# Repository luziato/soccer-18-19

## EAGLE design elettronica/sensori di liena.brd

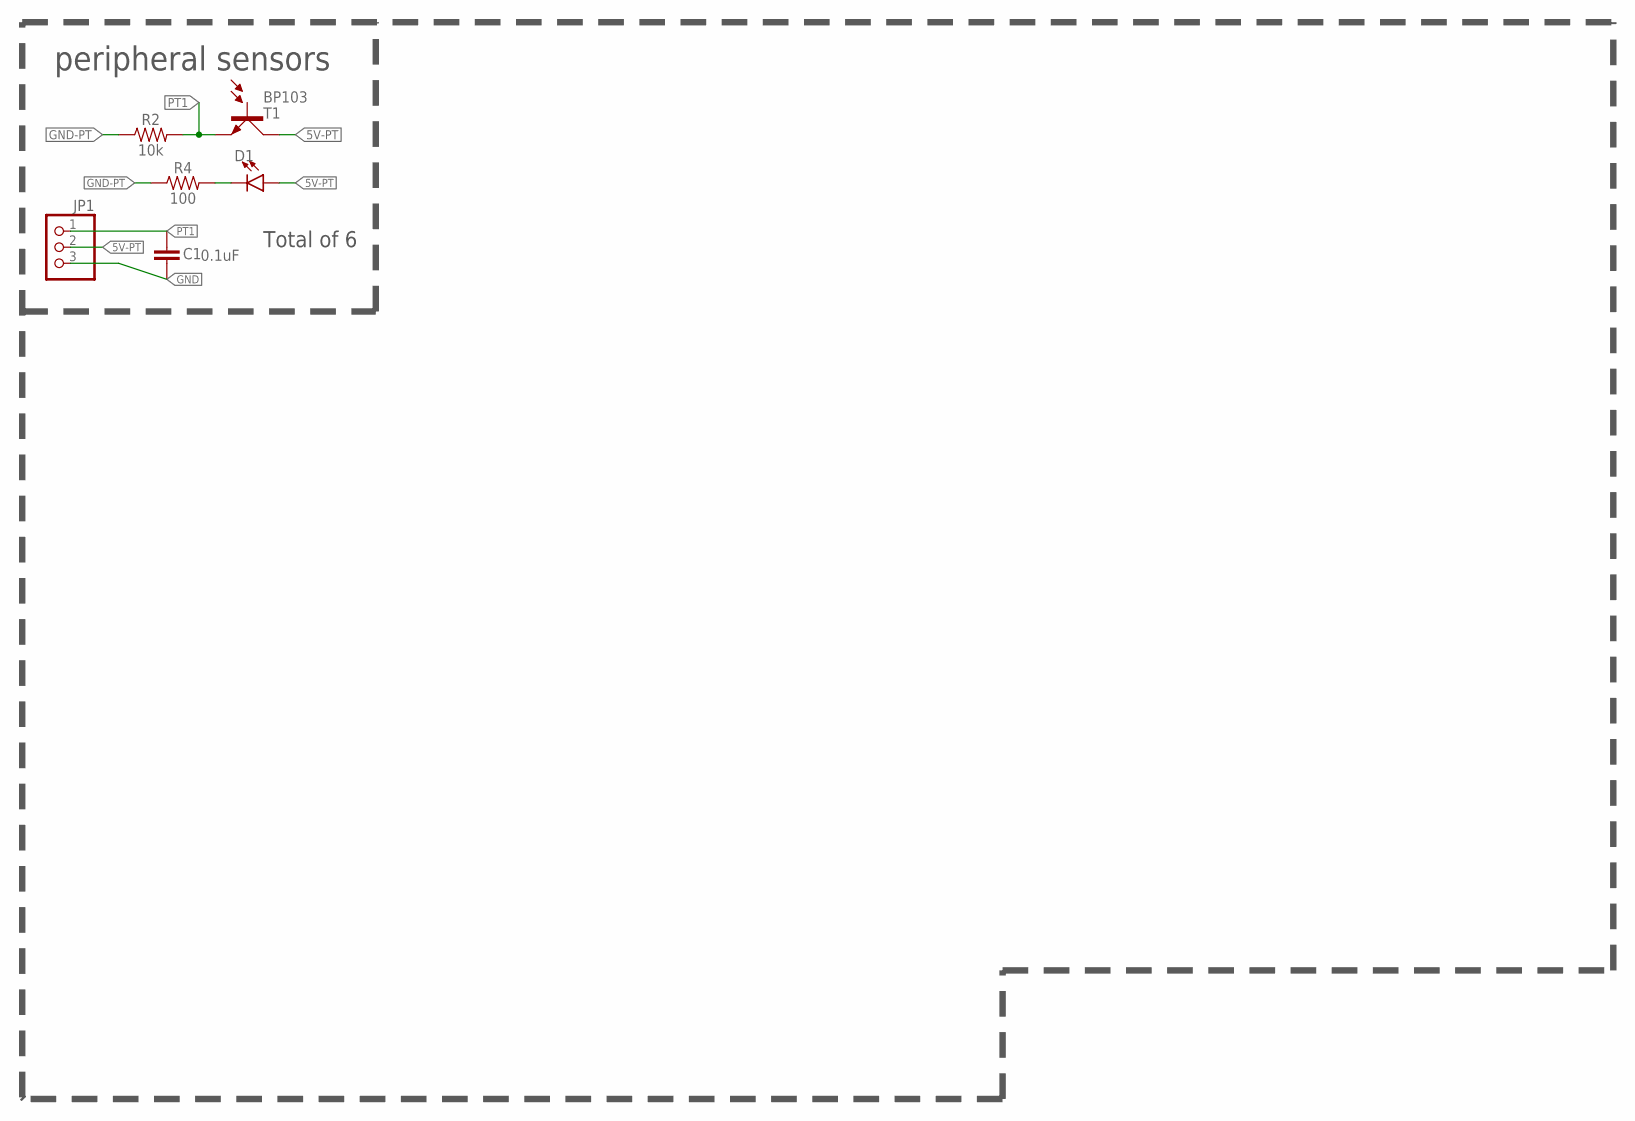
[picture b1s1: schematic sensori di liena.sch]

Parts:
C1: 0.1uF; CAP-PTH-SMALL-KIT
D1: LED3MM; LED_3MM
JP1: PINHD-1X3; 1X03
R2: 10k; 0603
R4: 100; 0603
T1: BP103

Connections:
5V-PT: D1.A, JP1.2, T1.C
GND: C1.2, JP1.3
GND-PT: R2.1, R4.1
unnamed: D1.K (C), R4.2
PT1: C1.1, JP1.1, R2.2, T1.E

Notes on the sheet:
peripheral sensors
Total of 6

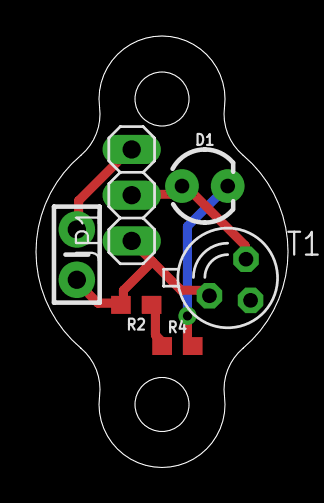
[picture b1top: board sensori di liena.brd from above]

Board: 2 copper layers, 14.0 x 24.0 mm, 6 parts (0 on the bottom side), 5 nets.

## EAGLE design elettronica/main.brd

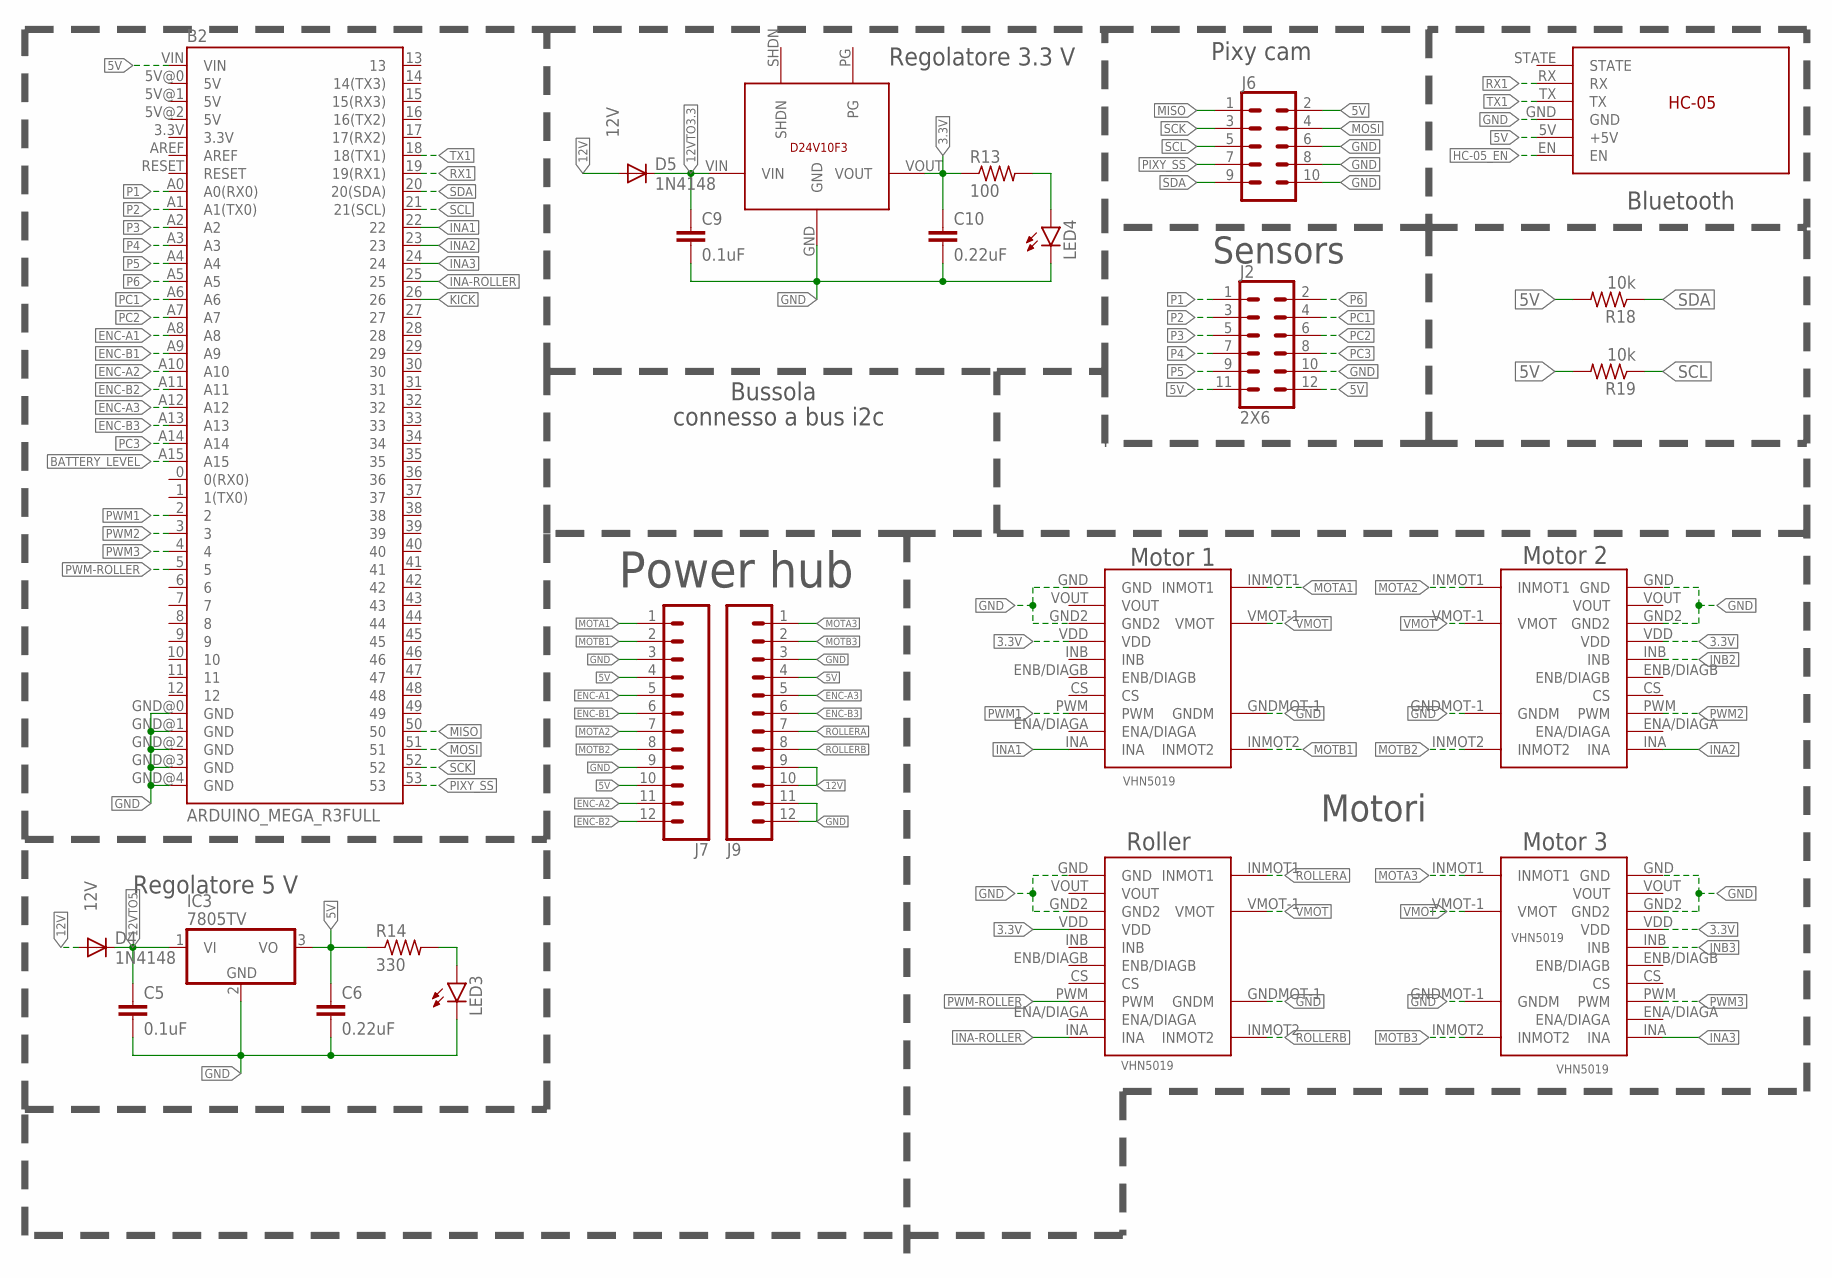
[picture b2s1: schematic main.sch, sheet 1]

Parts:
B2: ARDUINO_MEGA_R3FULL; ARDUINO_MEGA
C5, C9: 0.1uF; CAP-PTH-SMALL-KIT
C6, C10: 0.22uF; CAP-PTH-SMALL-KIT
D4, D5: 1N4148; DO35-7
IC3: 7805TV; TO220V
J2: 2X6
J6: CONN_05X2PTH; 2X5
J7, J9: CONN_12; 1X12
LED3, LED4: GREEN; LED-1206
R13: 100; M1206
R14: 330; M1206
R18, R19: 10k; M1206
U$4, U$5, U$6, U$7: VHN5019; MOTOR-SHIELD
U$18: HC-05
U$19: STEPDOWN_D24V10F3

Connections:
3.3V: C10.1, R13.1, U$4.VDD, U$5.VDD, U$6.VDD, U$7.VDD, U$19.VOUT; also elsewhere on the board
5V: B2.VIN, C6.1, IC3.3 (VO), J2.11, J2.12, J6.2, J7.4, J7.10, J9.4, R14.1, R18.2, R19.2, U$18.5V (+5V); also elsewhere on the board
12V: D4.A, D5.A, J9.9, J9.10; also elsewhere on the board
12VTO3.3: C9.1, D5.C, U$19.VIN
12VTO5: C5.1, D4.C, IC3.1 (VI)
BATTERY_LEVEL: B2.A15; also elsewhere on the board
ENC-A1: B2.A8, J7.5
ENC-A2: B2.A10, J7.11
ENC-A3: B2.A12, J9.5
ENC-B1: B2.A9, J7.6
ENC-B2: B2.A11, J7.12
ENC-B3: B2.A13, J9.6
GND: B2.GND@0 (GND), B2.GND@1 (GND), B2.GND@2 (GND), B2.GND@3 (GND), B2.GND@4 (GND), C5.2, C6.2, C9.2, C10.2, IC3.2 (GND), J2.10, J6.6, J6.8, J6.10, J7.3, J7.9, J9.3, J9.11, J9.12, LED3.C, LED4.C, U$4.GND, U$4.GND2, U$4.GNDMOT-1 (GNDM), U$5.GND, U$5.GND2, U$5.GNDMOT-1 (GNDM), U$6.GND, U$6.GND2, U$6.GNDMOT-1 (GNDM), U$7.GND, U$7.GND2, U$7.GNDMOT-1 (GNDM), U$18.GND, U$19.GND; also elsewhere on the board
HC-05_EN: U$18.EN
INA1: B2.22, U$4.INA
INA2: B2.23, U$5.INA
INA3: B2.24, U$6.INA
INA-ROLLER: B2.25, U$7.INA
INB2: U$5.INB
INB3: U$6.INB
KICK: B2.26; also elsewhere on the board
MISO: B2.50, J6.1
MOSI: B2.51, J6.4
MOTA1: J7.1, U$4.INMOT1
MOTA2: J7.7, U$5.INMOT1
MOTA3: J9.1, U$6.INMOT1
MOTB1: J7.2, U$4.INMOT2
MOTB2: J7.8, U$5.INMOT2
MOTB3: J9.2, U$6.INMOT2
unnamed: LED3.A, R14.2
unnamed: LED4.A, R13.2
P1: B2.A0 (A0(RX0)), J2.1
P2: B2.A1 (A1(TX0)), J2.3
P3: B2.A2, J2.5
P4: B2.A3, J2.7
P5: B2.A4, J2.9
P6: B2.A5, J2.2
PC1: B2.A6, J2.4
PC2: B2.A7, J2.6
PC3: B2.A14, J2.8
PIXY_SS: B2.53, J6.7
PWM1: B2.2, U$4.PWM
PWM2: B2.3, U$5.PWM
PWM3: B2.4, U$6.PWM
PWM-ROLLER: B2.5, U$7.PWM
ROLLERA: J9.7, U$7.INMOT1
ROLLERB: J9.8, U$7.INMOT2
RX1: B2.19 (19(RX1)), U$18.RX
SCK: B2.52, J6.3
SCL: B2.21 (21(SCL)), J6.5, R19.1; also elsewhere on the board
SDA: B2.20 (20(SDA)), J6.9, R18.1; also elsewhere on the board
TX1: B2.18 (18(TX1)), U$18.TX
VMOT: U$4.VMOT-1 (VMOT), U$5.VMOT-1 (VMOT), U$6.VMOT-1 (VMOT), U$7.VMOT-1 (VMOT); also elsewhere on the board

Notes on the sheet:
Regolatore 5 V
Regolatore 3.3 V
Bluetooth
Bussola
Motori
Roller
Motor 1
Motor 2
Motor 3
Pixy cam
Sensors
Power hub
connesso a bus i2c

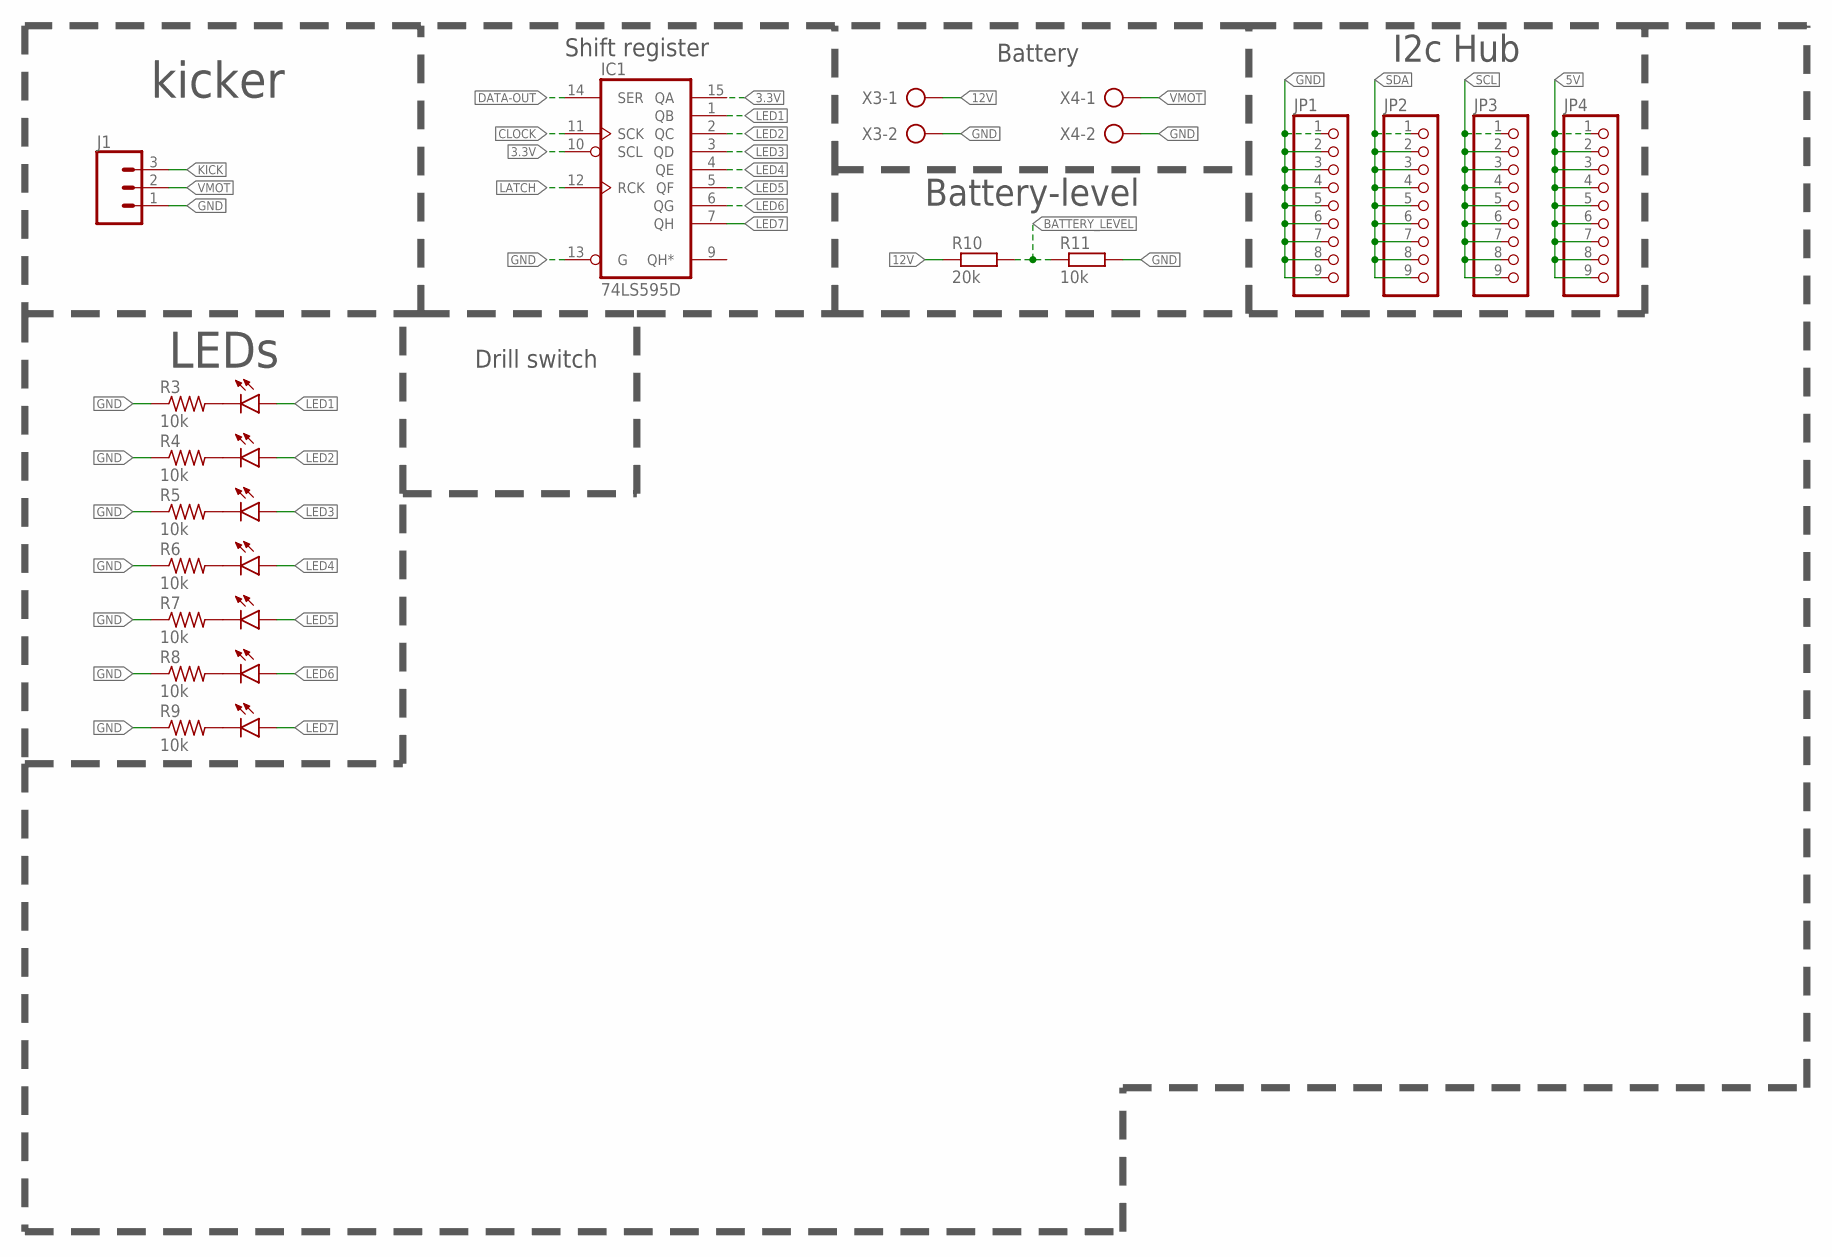
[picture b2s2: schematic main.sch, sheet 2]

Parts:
D1, D3, D6, D7, D8, D9, D10: GREEN; LED-1206
IC1: 74LS595D; SO16
J1: CONN_03; 1X03
JP1, JP2, JP3, JP4: PINHD-1X9; 1X09-BIG
R3, R4, R5, R6, R7, R8, R9: 10k; M1206
R10: 20k; 0204/7
R11: 10k; 0204/7
X3, X4: AK500/2-H

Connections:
3.3V: IC1.10 (SCL), IC1.15 (QA); also elsewhere on the board
5V: JP4.1, JP4.2, JP4.3, JP4.4, JP4.5, JP4.6, JP4.7, JP4.8, JP4.9; also elsewhere on the board
12V: R10.1, X3.1; also elsewhere on the board
BATTERY_LEVEL: R10.2, R11.1; also elsewhere on the board
CLOCK: IC1.11 (SCK)
DATA-OUT: IC1.14 (SER)
GND: IC1.8 (GND), IC1.13 (G), J1.1, JP1.1, JP1.2, JP1.3, JP1.4, JP1.5, JP1.6, JP1.7, JP1.8, JP1.9, R3.1, R4.1, R5.1, R6.1, R7.1, R8.1, R9.1, R11.2, X3.2, X4.2; also elsewhere on the board
KICK: J1.3; also elsewhere on the board
LATCH: IC1.12 (RCK)
LED1: D1.A, IC1.1 (QB)
LED2: D3.A, IC1.2 (QC)
LED3: D6.A, IC1.3 (QD)
LED4: D7.A, IC1.4 (QE)
LED5: D8.A, IC1.5 (QF)
LED6: D9.A, IC1.6 (QG)
LED7: D10.A, IC1.7 (QH)
unnamed: D1.C, R3.2
unnamed: D3.C, R4.2
unnamed: D6.C, R5.2
unnamed: D7.C, R6.2
unnamed: D8.C, R7.2
unnamed: D9.C, R8.2
unnamed: D10.C, R9.2
SCL: JP3.1, JP3.2, JP3.3, JP3.4, JP3.5, JP3.6, JP3.7, JP3.8, JP3.9; also elsewhere on the board
SDA: JP2.1, JP2.2, JP2.3, JP2.4, JP2.5, JP2.6, JP2.7, JP2.8, JP2.9; also elsewhere on the board
VCC: IC1.16 (VCC)
VMOT: J1.2, X4.1; also elsewhere on the board

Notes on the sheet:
Shift register
Battery
LEDs
Battery-level
Drill switch
I2c Hub
kicker

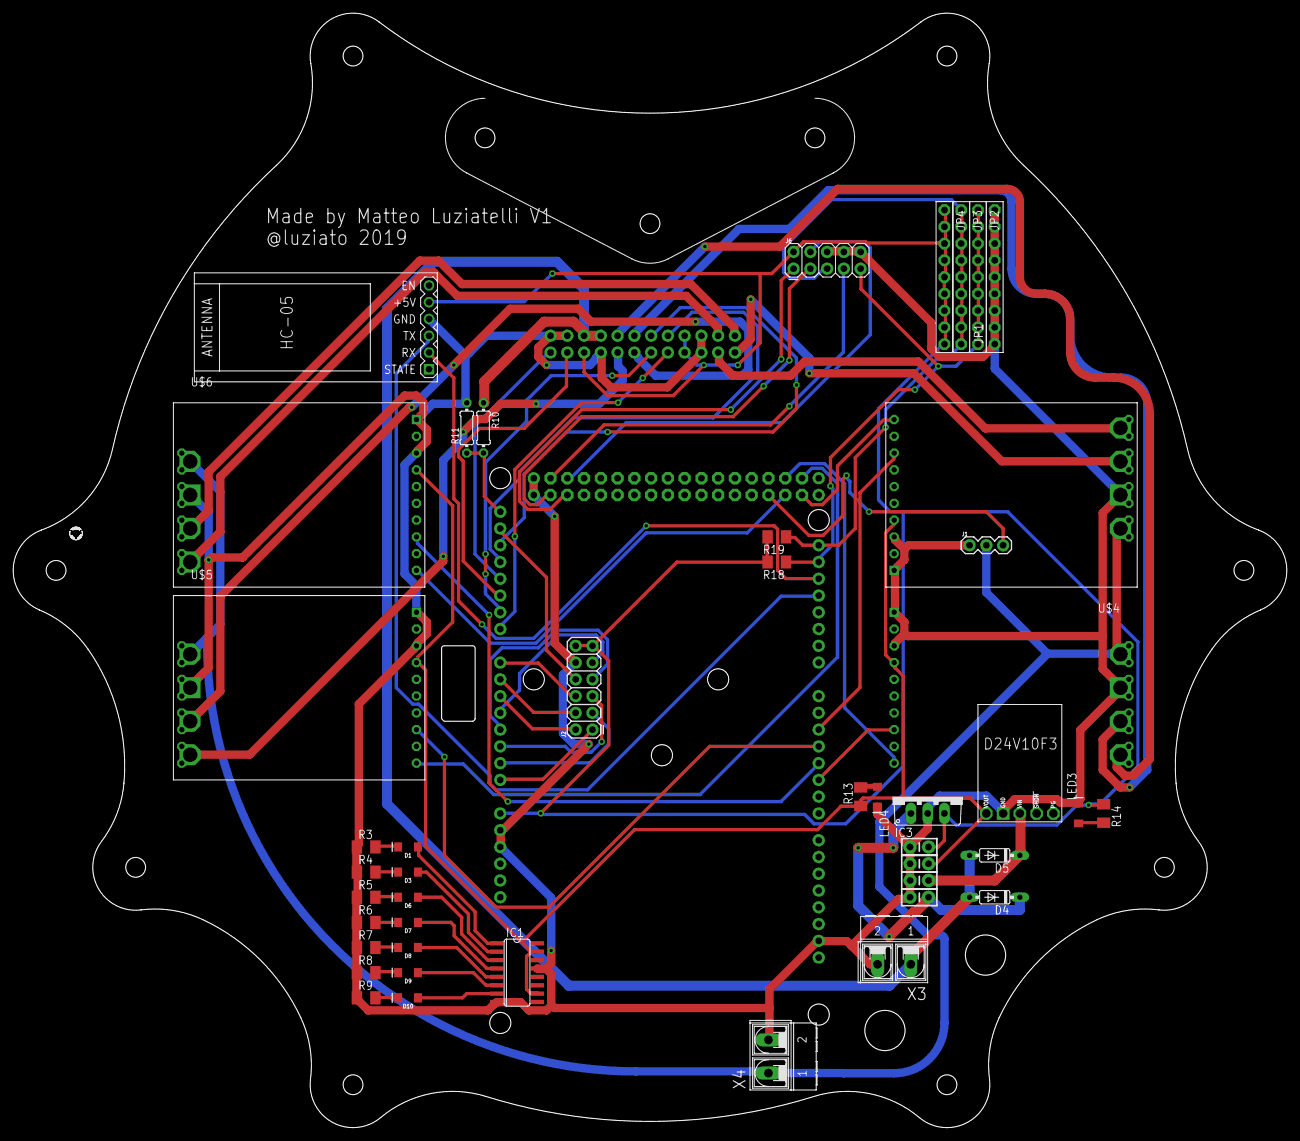
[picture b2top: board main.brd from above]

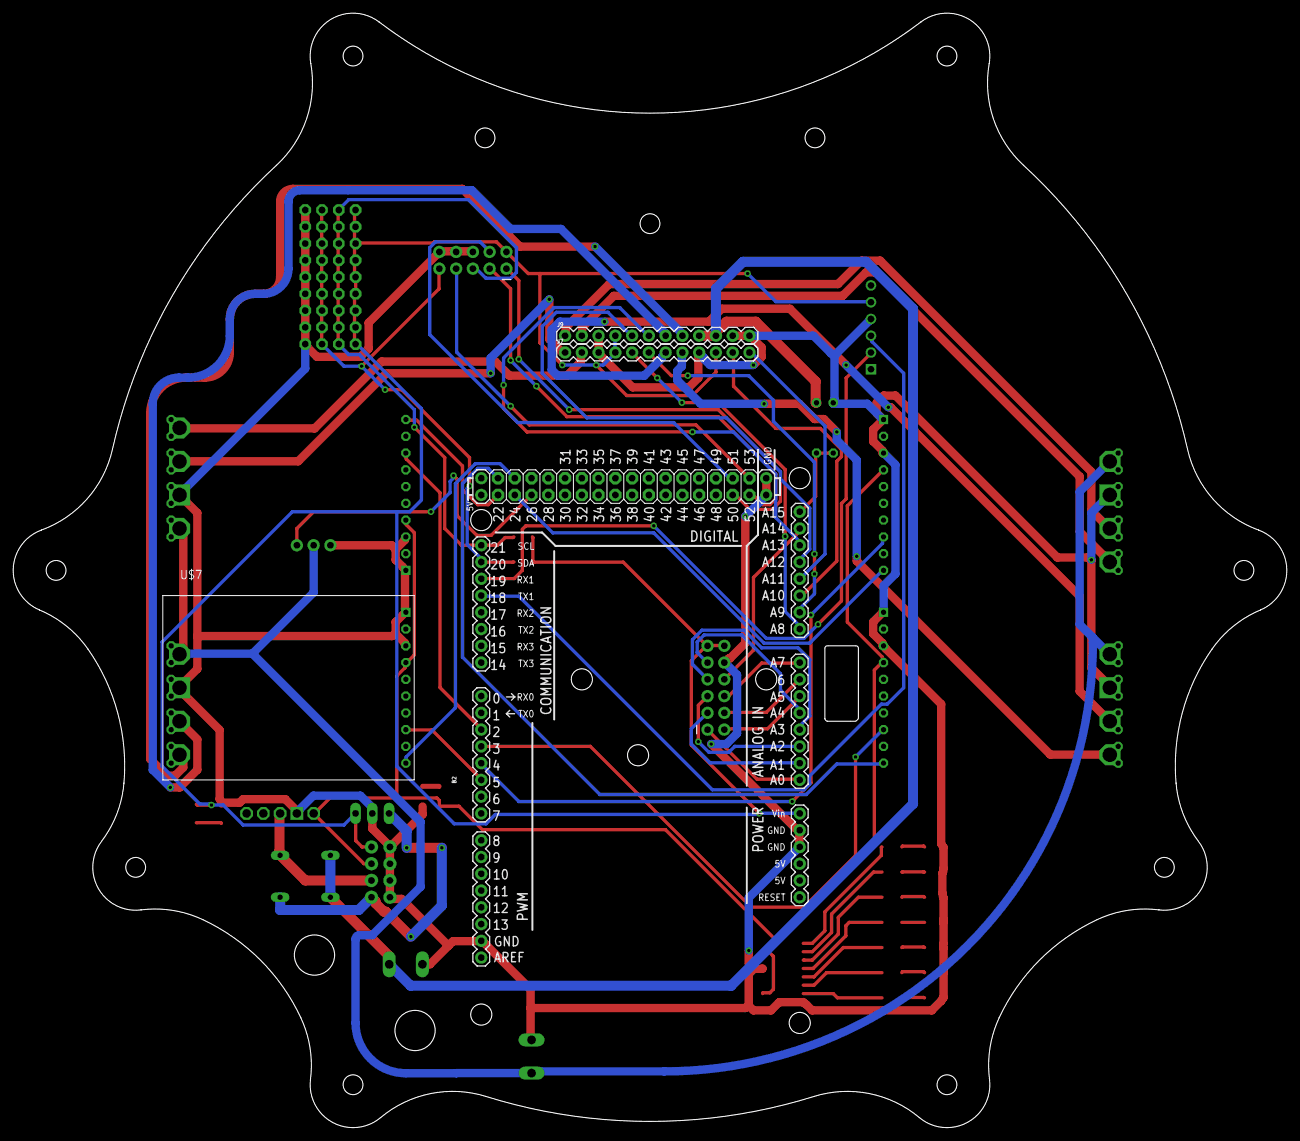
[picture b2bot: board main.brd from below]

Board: 2 copper layers, 193.0 x 168.9 mm, 48 parts (4 on the bottom side), 64 nets.

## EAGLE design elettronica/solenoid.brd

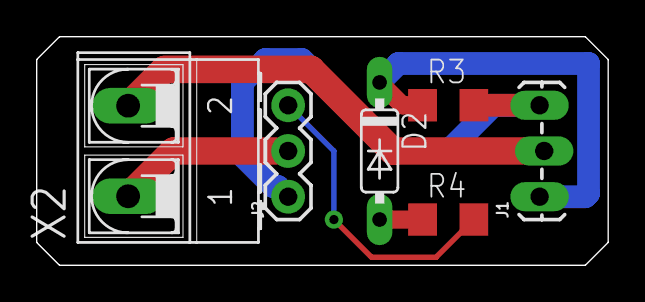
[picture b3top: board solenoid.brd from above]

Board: 2 copper layers, 31.8 x 12.7 mm, 6 parts (0 on the bottom side), 6 nets.

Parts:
D2: 1N4148; DO35-7
J1: stp16nf06; 1X03_LOCK_LONGPADS
J2: 1X03
R3: 10k; R1206
R4: 100; R1206
X2: AK500/2-H

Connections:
12V: J2.2, X2.1
DRAIN: J1.2, X2.2
GND: J1.3, J2.1, R3.2
KICK: J2.3, R4.2
unnamed: D2.C, J1.1, R3.1
unnamed: D2.A, R4.1

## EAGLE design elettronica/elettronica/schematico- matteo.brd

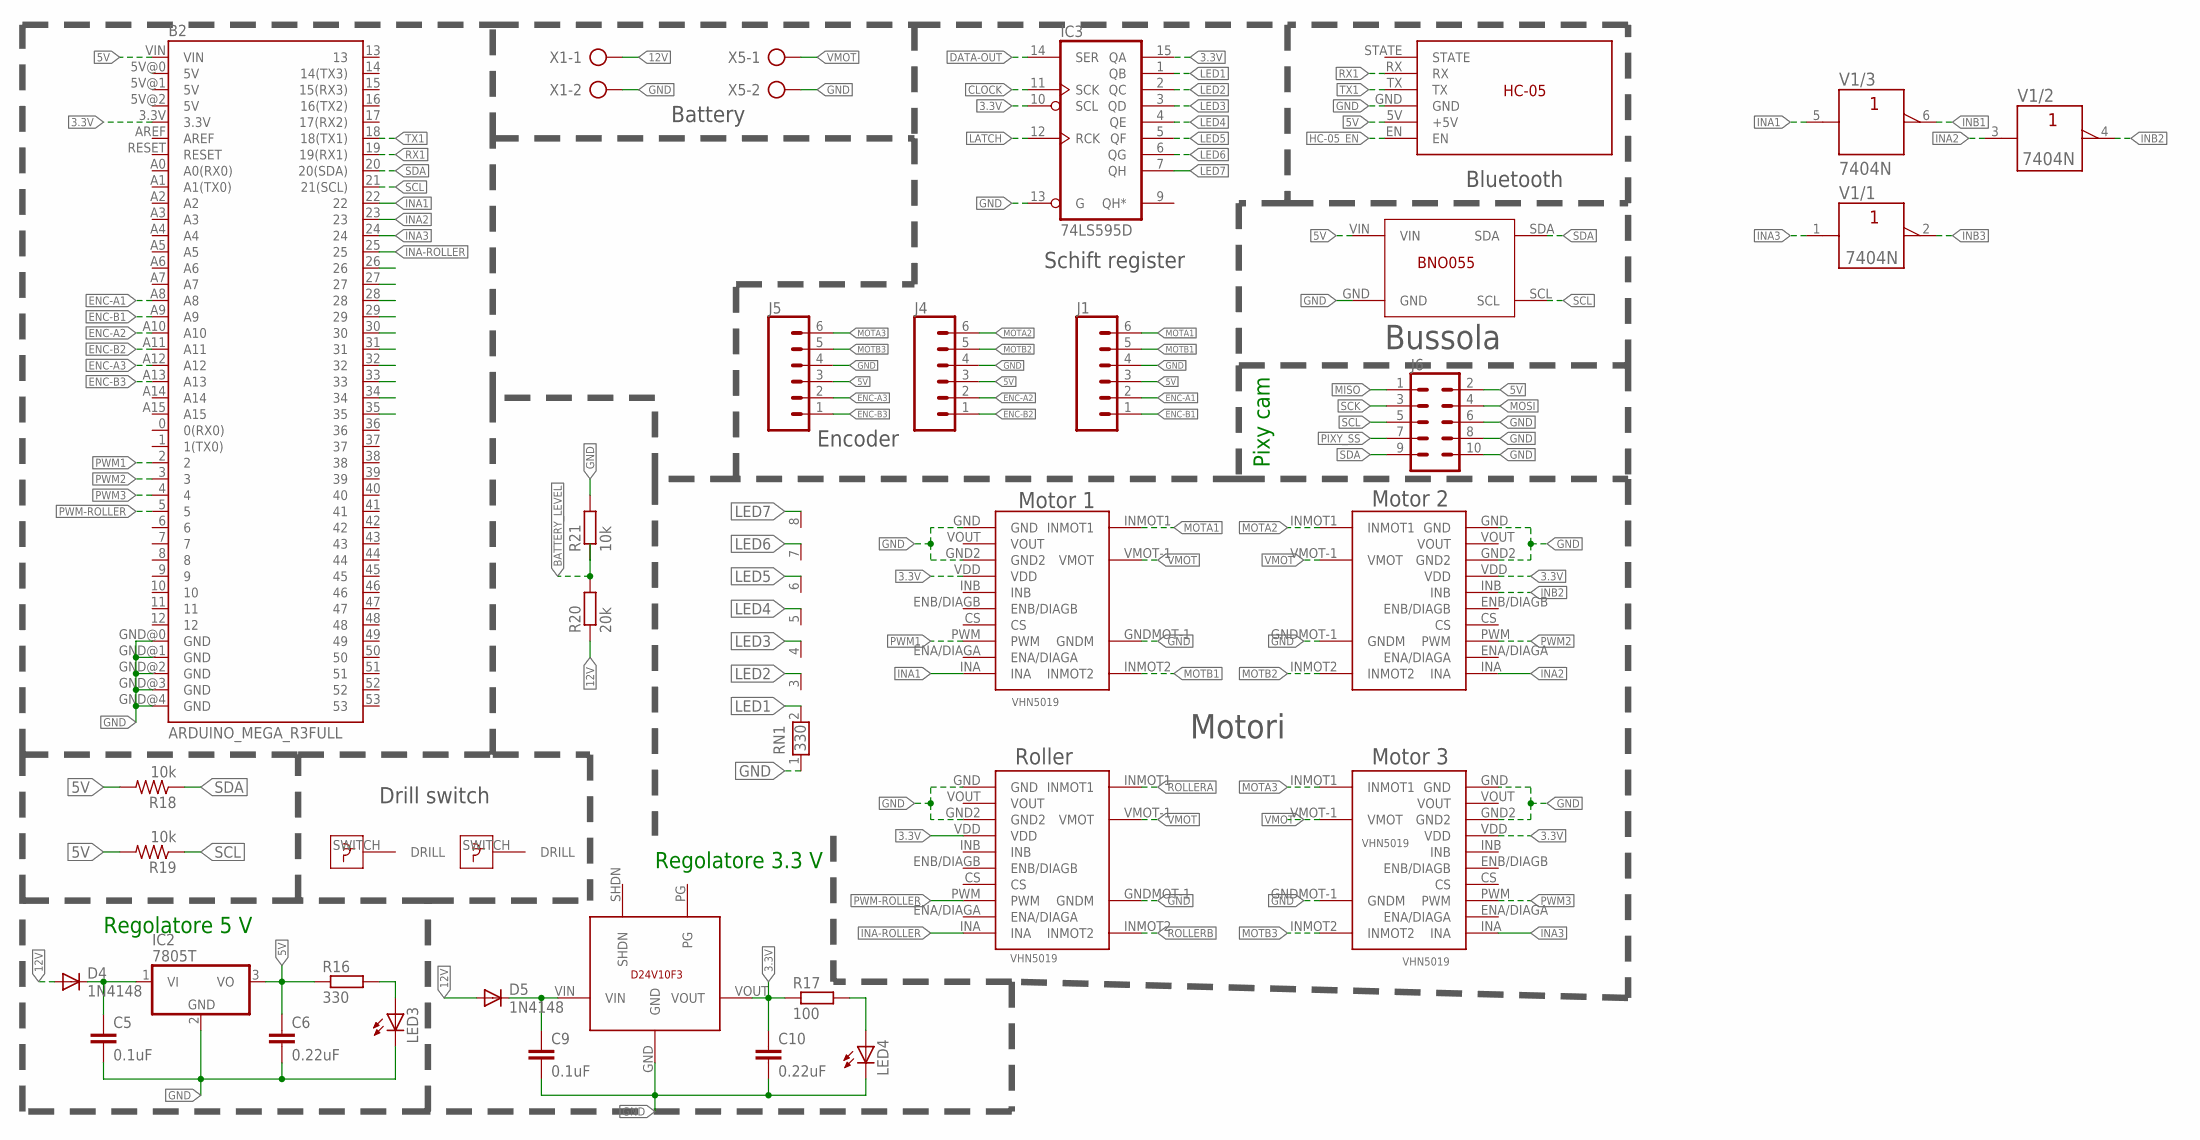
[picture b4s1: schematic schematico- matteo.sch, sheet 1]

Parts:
B2: ARDUINO_MEGA_R3FULL; ARDUINO_MEGA
C5, C9: 0.1uF; CAP-PTH-SMALL-KIT
C6, C10: 0.22uF; CAP-PTH-SMALL-KIT
D4, D5: 1N4148; DO35-7
IC2: 7805T; TO220H
IC3: 74LS595D; SO16
J1, J4, J5: CONN_06SILK_FEMALE_PTH; 1X06
J6: CONN_05X2PTH; 2X5
LED3, LED4: TLLR4400; LED3MM
R16: 330; 0204/7
R17: 100; 0204/7
R18, R19: 10k; M1206
R20: 20k; 0204/7
R21: 10k; 0204/7
RN1: 330; RN-8
U$1, U$2: DRILL_SWITCH
U$4, U$5, U$6, U$7: VHN5019; MOTOR-SHIELD
U$17: BNO055; BNO005
U$18: HC-05
U$19: STEPDOWN_D24V10F3
V1: 7404N; DIL14
X1, X5: AK500/2-H

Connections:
3.3V: B2.3.3V, C10.1, IC3.10 (SCL), IC3.15 (QA), R17.1, U$4.VDD, U$5.VDD, U$6.VDD, U$7.VDD, U$19.VOUT; also elsewhere on the board
5V: B2.VIN, C6.1, IC2.3 (VO), J1.3, J4.3, J5.3, J6.2, R16.1, R18.2, R19.2, U$17.VIN, U$18.5V (+5V); also elsewhere on the board
12V: C5.1, D4.A, D4.C, D5.A, IC2.1 (VI), R20.1, X1.1; also elsewhere on the board
+UB: V1.14 (+UB)
-UB: V1.7 (-UB)
BATTERY_LEVEL: R20.2, R21.1; also elsewhere on the board
CLOCK: IC3.11 (SCK)
DATA-OUT: IC3.14 (SER)
ENC-A1: B2.A8, J1.2
ENC-A2: B2.A10, J4.2
ENC-A3: B2.A12, J5.2
ENC-B1: B2.A9, J1.1
ENC-B2: B2.A11, J4.1
ENC-B3: B2.A13, J5.1
GND: B2.GND@0 (GND), B2.GND@1 (GND), B2.GND@2 (GND), B2.GND@3 (GND), B2.GND@4 (GND), C5.2, C6.2, C9.2, C10.2, IC2.2 (GND), IC3.8 (GND), IC3.13 (G), J1.4, J4.4, J5.4, J6.6, J6.8, J6.10, LED3.K (C), LED4.K (C), R21.2, RN1.1, U$4.GND, U$4.GND2, U$4.GNDMOT-1 (GNDM), U$5.GND, U$5.GND2, U$5.GNDMOT-1 (GNDM), U$6.GND, U$6.GND2, U$6.GNDMOT-1 (GNDM), U$7.GND, U$7.GND2, U$7.GNDMOT-1 (GNDM), U$17.GND, U$18.GND, U$19.GND, X1.2, X5.2; also elsewhere on the board
HC-05_EN: U$18.EN
INA1: B2.22, U$4.INA, V1.5 (A)
INA2: B2.23, U$5.INA, V1.3 (A)
INA3: B2.24, U$6.INA, V1.1 (A)
INA-ROLLER: B2.25, U$7.INA
INB1: V1.6 (Y)
INB2: U$5.INB, V1.4 (Y)
INB3: V1.2 (Y)
LATCH: IC3.12 (RCK)
LED1: IC3.1 (QB), RN1.2; also elsewhere on the board
LED2: IC3.2 (QC), RN1.3; also elsewhere on the board
LED3: IC3.3 (QD), RN1.4; also elsewhere on the board
LED4: IC3.4 (QE), RN1.5; also elsewhere on the board
LED5: IC3.5 (QF), RN1.6; also elsewhere on the board
LED6: IC3.6 (QG), RN1.7; also elsewhere on the board
LED7: IC3.7 (QH), RN1.8; also elsewhere on the board
MISO: J6.1; also elsewhere on the board
MOSI: J6.4; also elsewhere on the board
MOTA1: J1.6, U$4.INMOT1
MOTA2: J4.6, U$5.INMOT1
MOTA3: J5.6, U$6.INMOT1
MOTB1: J1.5, U$4.INMOT2
MOTB2: J4.5, U$5.INMOT2
MOTB3: J5.5, U$6.INMOT2
unnamed: LED3.A, R16.2
unnamed: C9.1, D5.C, U$19.VIN
unnamed: LED4.A, R17.2
PIXY_SS: J6.7; also elsewhere on the board
PWM1: B2.2, U$4.PWM
PWM2: B2.3, U$5.PWM
PWM3: B2.4, U$6.PWM
PWM-ROLLER: B2.5, U$7.PWM
ROLLERA: U$7.INMOT1
ROLLERB: U$7.INMOT2
RX1: B2.19 (19(RX1)), U$18.RX
SCK: J6.3; also elsewhere on the board
SCL: B2.21 (21(SCL)), J6.5, R19.1, U$17.SCL; also elsewhere on the board
SDA: B2.20 (20(SDA)), J6.9, R18.1, U$17.SDA; also elsewhere on the board
TX1: B2.18 (18(TX1)), U$18.TX
VCC: IC3.16 (VCC)
VMOT: U$4.VMOT-1 (VMOT), U$5.VMOT-1 (VMOT), U$6.VMOT-1 (VMOT), U$7.VMOT-1 (VMOT), X5.1; also elsewhere on the board

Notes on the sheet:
Regolatore 5 V
Regolatore 3.3 V
Encoder
Schift register
Bluetooth
Bussola
Motori
Roller
Battery
Drill switch
Motor 1
Motor 2
Motor 3
Pixy cam

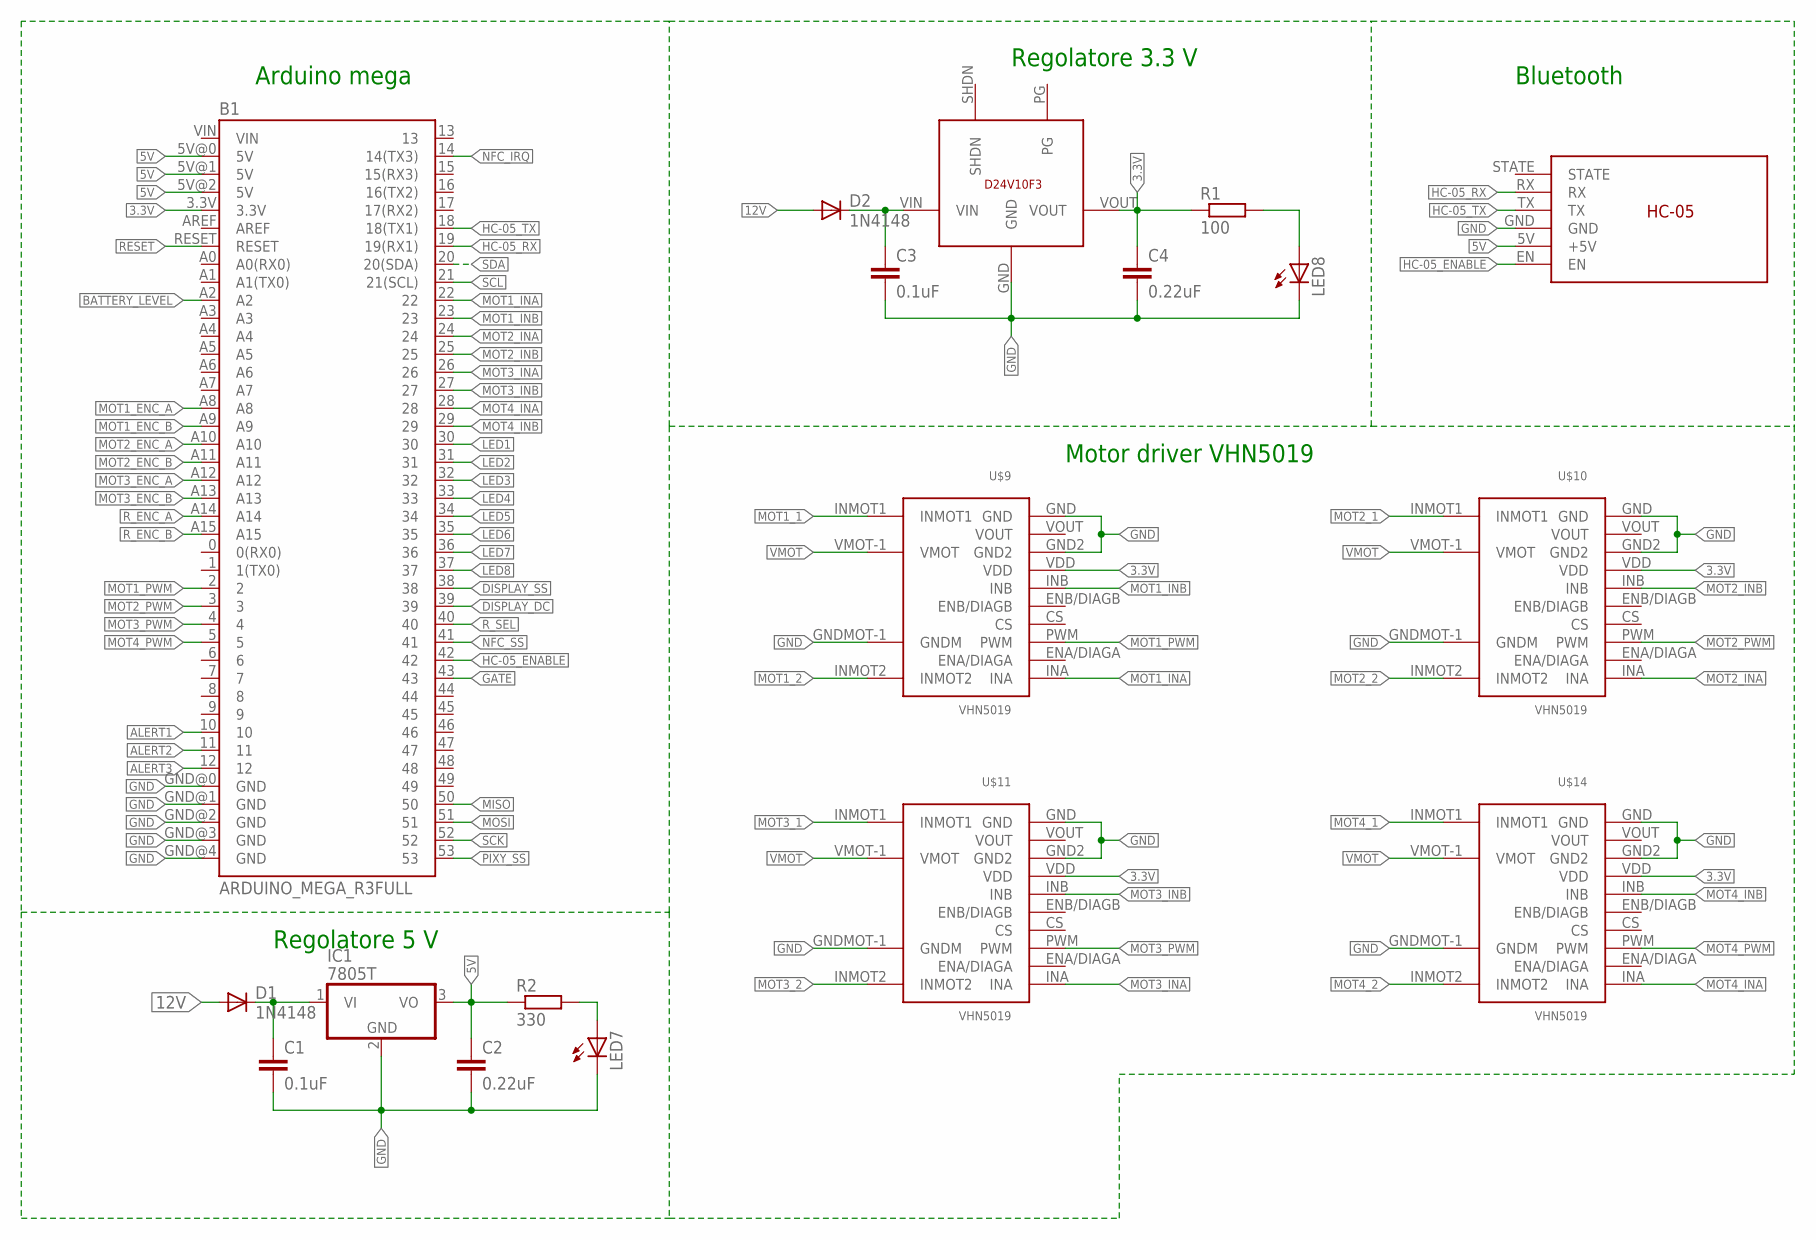
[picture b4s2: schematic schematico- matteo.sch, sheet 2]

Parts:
B1: ARDUINO_MEGA_R3FULL; ARDUINO_MEGA
C1, C3: 0.1uF; CAP-PTH-SMALL-KIT
C2, C4: 0.22uF; CAP-PTH-SMALL-KIT
D1, D2: 1N4148; DO35-7
IC1: 7805T; TO220H
LED7, LED8: TLLR4400; LED3MM
R1: 100; 0204/7
R2: 330; 0204/7
U$8: STEPDOWN_D24V10F3
U$9, U$10, U$11, U$14: VHN5019; MOTOR-SHIELD
U$16: HC-05

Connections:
3.3V: B1.3.3V, C4.1, R1.1, U$8.VOUT, U$9.VDD, U$10.VDD, U$11.VDD, U$14.VDD; also elsewhere on the board
5V: B1.5V@0 (5V), B1.5V@1 (5V), B1.5V@2 (5V), C2.1, IC1.3 (VO), R2.1, U$16.5V (+5V); also elsewhere on the board
12V: C1.1, D1.A, D1.C, D2.A, IC1.1 (VI); also elsewhere on the board
ALERT1: B1.10; also elsewhere on the board
ALERT2: B1.11; also elsewhere on the board
ALERT3: B1.12; also elsewhere on the board
BATTERY_LEVEL: B1.A2; also elsewhere on the board
DISPLAY_DC: B1.39; also elsewhere on the board
DISPLAY_SS: B1.38; also elsewhere on the board
GATE: B1.43; also elsewhere on the board
GND: B1.GND@0 (GND), B1.GND@1 (GND), B1.GND@2 (GND), B1.GND@3 (GND), B1.GND@4 (GND), C1.2, C2.2, C3.2, C4.2, IC1.2 (GND), LED7.K (C), LED8.K (C), U$8.GND, U$9.GND, U$9.GND2, U$9.GNDMOT-1 (GNDM), U$10.GND, U$10.GND2, U$10.GNDMOT-1 (GNDM), U$11.GND, U$11.GND2, U$11.GNDMOT-1 (GNDM), U$14.GND, U$14.GND2, U$14.GNDMOT-1 (GNDM), U$16.GND; also elsewhere on the board
HC-05_ENABLE: B1.42, U$16.EN
HC-05_RX: B1.19 (19(RX1)), U$16.RX
HC-05_TX: B1.18 (18(TX1)), U$16.TX
LED1: B1.30; also elsewhere on the board
LED2: B1.31; also elsewhere on the board
LED3: B1.32; also elsewhere on the board
LED4: B1.33; also elsewhere on the board
LED5: B1.34; also elsewhere on the board
LED6: B1.35; also elsewhere on the board
LED7: B1.36; also elsewhere on the board
LED8: B1.37; also elsewhere on the board
MISO: B1.50; also elsewhere on the board
MOSI: B1.51; also elsewhere on the board
MOT1_1: U$9.INMOT1; also elsewhere on the board
MOT1_2: U$9.INMOT2; also elsewhere on the board
MOT1_ENC_A: B1.A8; also elsewhere on the board
MOT1_ENC_B: B1.A9; also elsewhere on the board
MOT1_INA: B1.22, U$9.INA
MOT1_INB: B1.23, U$9.INB
MOT1_PWM: B1.2, U$9.PWM
MOT2_1: U$10.INMOT1; also elsewhere on the board
MOT2_2: U$10.INMOT2; also elsewhere on the board
MOT2_ENC_A: B1.A10; also elsewhere on the board
MOT2_ENC_B: B1.A11; also elsewhere on the board
MOT2_INA: B1.24, U$10.INA
MOT2_INB: B1.25, U$10.INB
MOT2_PWM: B1.3, U$10.PWM
MOT3_1: U$11.INMOT1; also elsewhere on the board
MOT3_2: U$11.INMOT2; also elsewhere on the board
MOT3_ENC_A: B1.A12; also elsewhere on the board
MOT3_ENC_B: B1.A13; also elsewhere on the board
MOT3_INA: B1.26, U$11.INA
MOT3_INB: B1.27, U$11.INB
MOT3_PWM: B1.4, U$11.PWM
MOT4_1: U$14.INMOT1
MOT4_2: U$14.INMOT2
MOT4_INA: B1.28, U$14.INA
MOT4_INB: B1.29, U$14.INB
MOT4_PWM: B1.5, U$14.PWM
unnamed: LED7.A, R2.2
unnamed: C3.1, D2.C, U$8.VIN
unnamed: LED8.A, R1.2
NFC_IRQ: B1.14 (14(TX3)); also elsewhere on the board
NFC_SS: B1.41; also elsewhere on the board
PIXY_SS: B1.53; also elsewhere on the board
RESET: B1.RESET; also elsewhere on the board
R_ENC_A: B1.A14; also elsewhere on the board
R_ENC_B: B1.A15; also elsewhere on the board
R_SEL: B1.40; also elsewhere on the board
SCK: B1.52; also elsewhere on the board
SCL: B1.21 (21(SCL)); also elsewhere on the board
SDA: B1.20 (20(SDA)); also elsewhere on the board
VMOT: U$9.VMOT-1 (VMOT), U$10.VMOT-1 (VMOT), U$11.VMOT-1 (VMOT), U$14.VMOT-1 (VMOT); also elsewhere on the board

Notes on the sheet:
Arduino mega
Regolatore 5 V
Motor driver VHN5019
Bluetooth
Regolatore 3.3 V

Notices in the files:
parts and their libraries:
SparkFun-Boards: Licensing: Creative Commons ShareAlike 4.0 International - https://creativecommons.org/licenses/by-sa/4.0
